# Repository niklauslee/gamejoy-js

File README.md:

# GamejoyJS

## Overview

A retro-style game console programmable with JavaScript.

- [Raspberry Pi Pico](https://www.raspberrypi.org/products/raspberry-pi-pico/) (RP2040)
- [Kaluma](https://kalumajs.org) is used for JavaScript runtime.
- 1.44" 16-bit color TFT LCD (128x128)
- Magnetic buzzer
- TP4056 charger with 500mAh LiPo battery
- PCB designed by KiCAD
- 3D-printed case (PLA)

__YouTube__

# Components

| Part                   | Quantity | Note   |
| ---------------------- | -------- | ------ |
| Raspberry Pi Pico      | 1        |  |
| Tactile Buttons        | 6        | ITS-1105RT(5mm) - [(devicemart)](https://www.devicemart.co.kr/goods/view?no=36627) |
| Slide Switch           | 1        | SK-12D02 - [(devicemart)](https://www.devicemart.co.kr/goods/view?no=14566) |
| Buzzer                 | 1        | Magnetic(IMT09B2703P) - [(devicemart)](https://www.devicemart.co.kr/goods/view?no=13992293) |
| LiPo Battery           | 1        | 500mAh (35mmx30mmx5mm) - [(devicemart)](https://www.devicemart.co.kr/goods/view?no=1360753) |
| TP4056 Battery Charger | 1        | SZH-EK026 (micro-USB) - [(aliexpress)](https://www.aliexpress.com/item/1005002629114871.html) |
| Custom PCB             | 1        | Designed with KiCAD, manufactured by [JLCPCB](https://jlcpcb.com/). KiCAD files in `kicad` folder |
| 1.44" TFT LCD (ST7735) | 1  | [(aliexpress)](https://www.aliexpress.com/item/32996979276.html) |
| Header Pins            |          | |
| 3D-printed case        |          | Designed with [Tinkercad](https://www.tinkercad.com/things/ey7LfFO1ldH). STL files in `design` folder |
| Tapping screws         | 4        | M3x8 |

## Preparations

Before uploading a game, please ensure that [Kaluma](https://kalumajs.org) firmware must be flashed in Raspberry Pi Pico.

[Kaluma CLI](https://github.com/kaluma-project/kaluma-cli) is also required to upload a game code.

## Upload Games

Currently only Tetris is available

- `./src/tetris.js`

Upload the Tetris game as below:

```sh
kaluma flash ./src/tetris --bundle --port <port>
```

## License

[MIT](LICENSE)

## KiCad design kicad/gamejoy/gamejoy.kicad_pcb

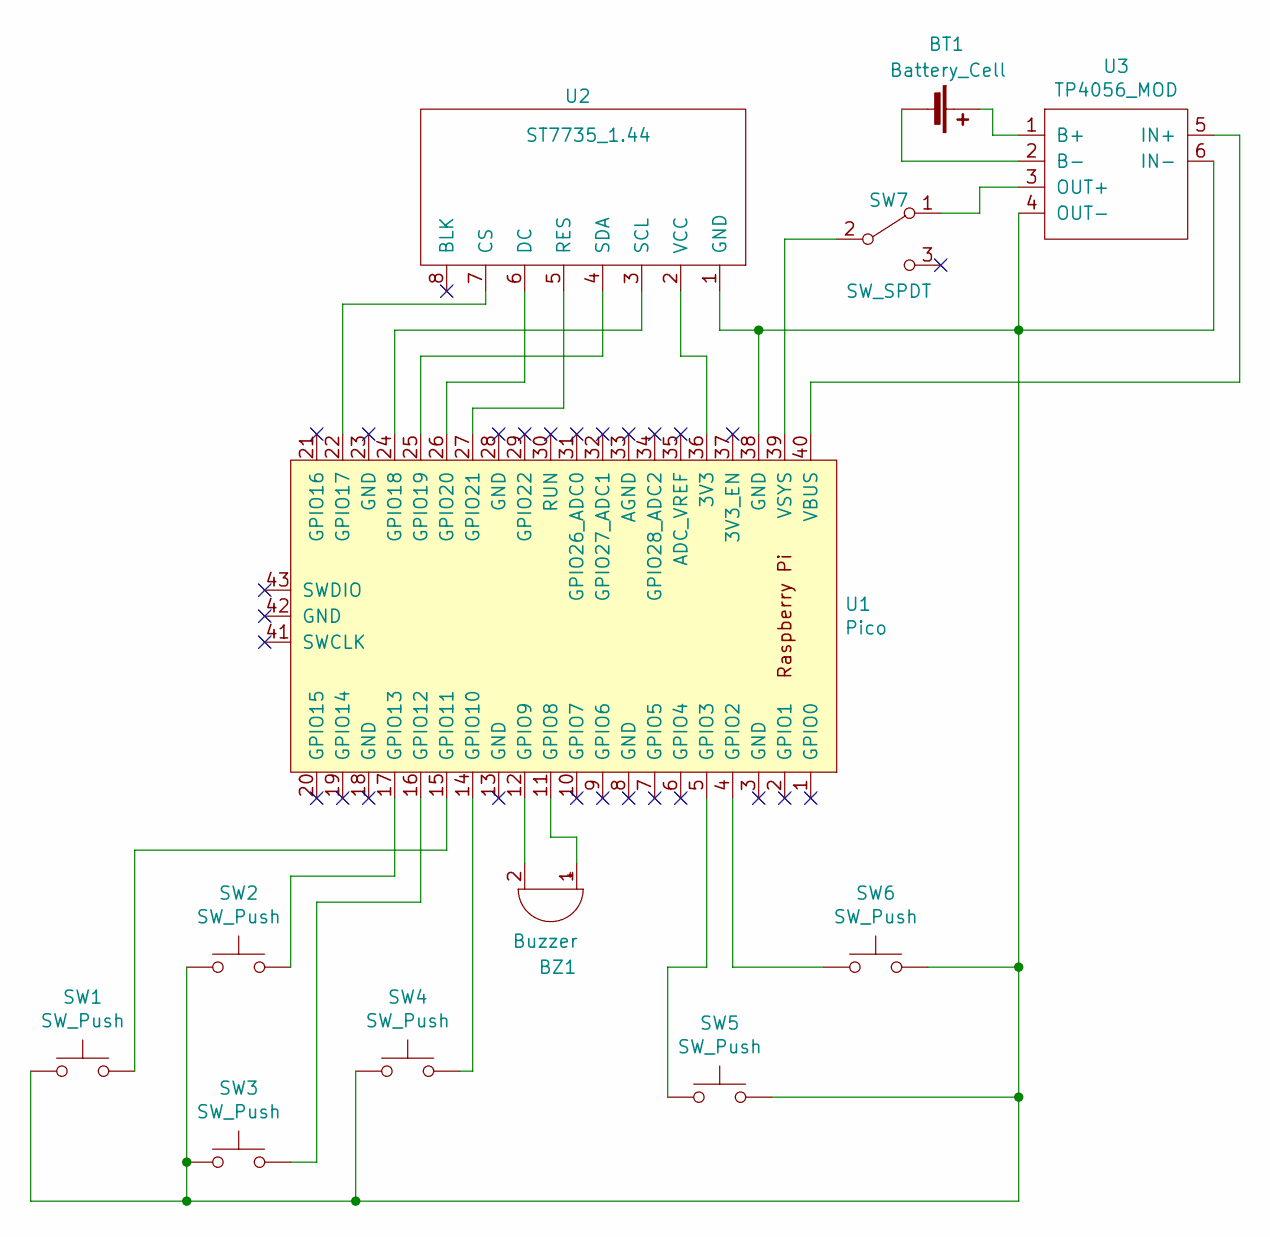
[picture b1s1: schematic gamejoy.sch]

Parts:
BT1: Battery_Cell; PinHeader_1x02_P2.54mm_Vertical
BZ1: Buzzer; MagneticBuzzer_PUI_AT-0927-TT-6-R
SW1, SW2, SW3, SW4, SW5, SW6: SW_Push; Button_Tactile_6.2mm_Square
SW7: SW_SPDT; SW_CuK_OS102011MA1QN1_SPDT_Angled
U1: Pico; RPi_Pico_SMD_TH
U2: ST7735_1.44; PinHeader_1x08_P2.54mm_Vertical
U3: TP4056_MOD

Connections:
unnamed: BT1.1 (+), U3.1 (B+)
unnamed: BT1.2 (-), U3.2 (B-)
unnamed: BZ1.1 (-), U1.11 (GPIO8)
unnamed: BZ1.2 (+), U1.12 (GPIO9)
unnamed: SW1.1, SW2.1, SW3.1, SW4.1, SW5.2, SW6.2, U1.38 (GND), U2.1 (GND), U3.4 (OUT-), U3.6 (IN-)
unnamed: SW1.2, U1.15 (GPIO11)
unnamed: SW2.2, U1.17 (GPIO13)
unnamed: SW3.2, U1.16 (GPIO12)
unnamed: SW4.2, U1.14 (GPIO10)
unnamed: SW5.1, U1.5 (GPIO3)
unnamed: SW6.1, U1.4 (GPIO2)
unnamed: SW7.1 (A), U3.3 (OUT+)
unnamed: SW7.2 (B), U1.39 (VSYS)
unnamed: U1.22 (GPIO17), U2.7 (CS)
unnamed: U1.24 (GPIO18), U2.3 (SCL)
unnamed: U1.25 (GPIO19), U2.4 (SDA)
unnamed: U1.26 (GPIO20), U2.6 (DC)
unnamed: U1.27 (GPIO21), U2.5 (RES)
unnamed: U1.36 (3V3), U2.2 (VCC)
unnamed: U1.40 (VBUS), U3.5 (IN+)

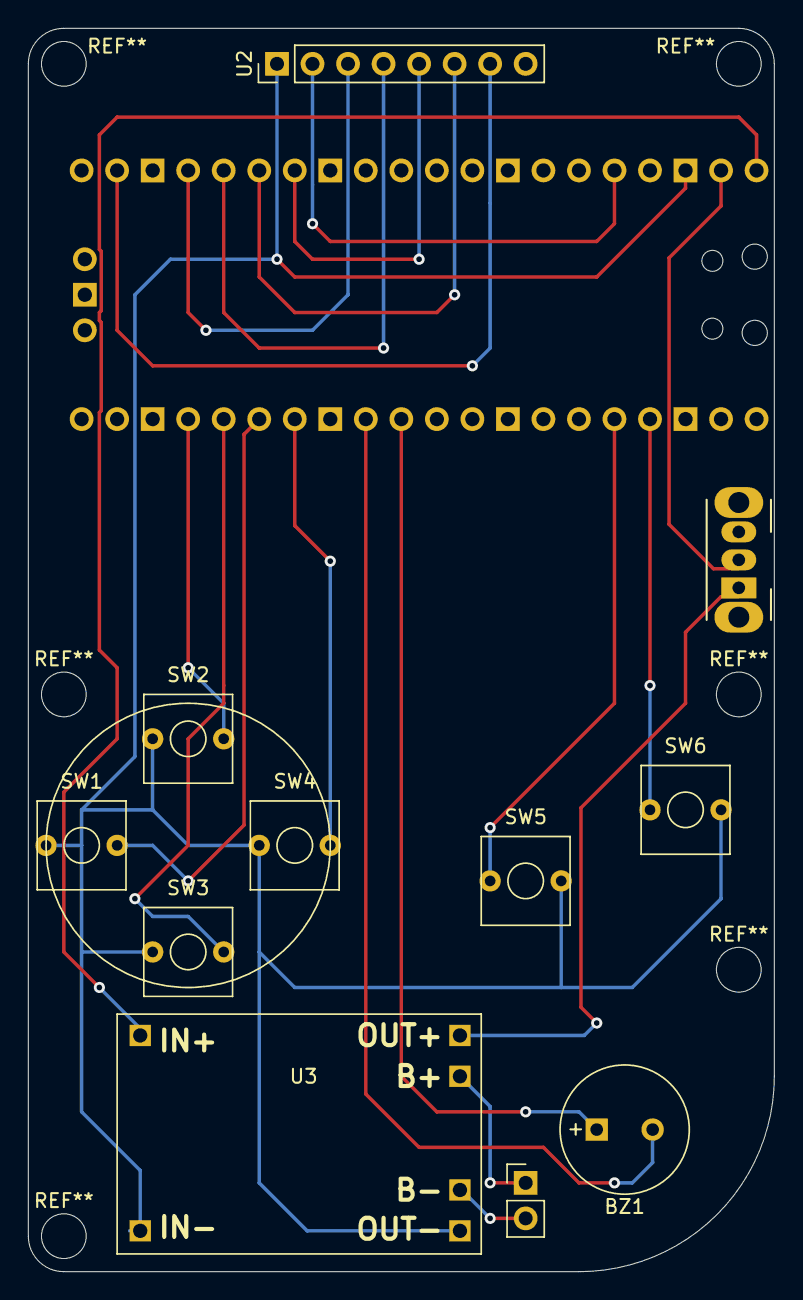
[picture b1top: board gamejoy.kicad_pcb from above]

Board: 2 copper layers, 53.3 x 88.9 mm, 12 parts (1 on the bottom side), 20 nets.

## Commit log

2022-02-13 Add src files
2022-02-16 Update for Kaluma CLI
2022-02-16 Remove unnecessary files
